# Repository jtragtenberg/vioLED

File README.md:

# vioLED
A guitar with LEDs on its frets

This instrument was developed by João Tragtenberg, Filipe Calegario from Batebit Artesania Digital (https://batebit.cc) in partnership with the string instruments luthier Rodrigo Veras (https://corpodusom.blogspot.com/) and the company Daccord Music Software (https://www.daccord.com.br/) as a first prototype for a acoustic guitar connected to a mobile app for educational purpuses.

Rodrigo his father and myself finishing the guitar

First time it lit

vioLED shining back to its maker Rodrigo Veras

Full lights in João's workshop

Example of chord progression mode

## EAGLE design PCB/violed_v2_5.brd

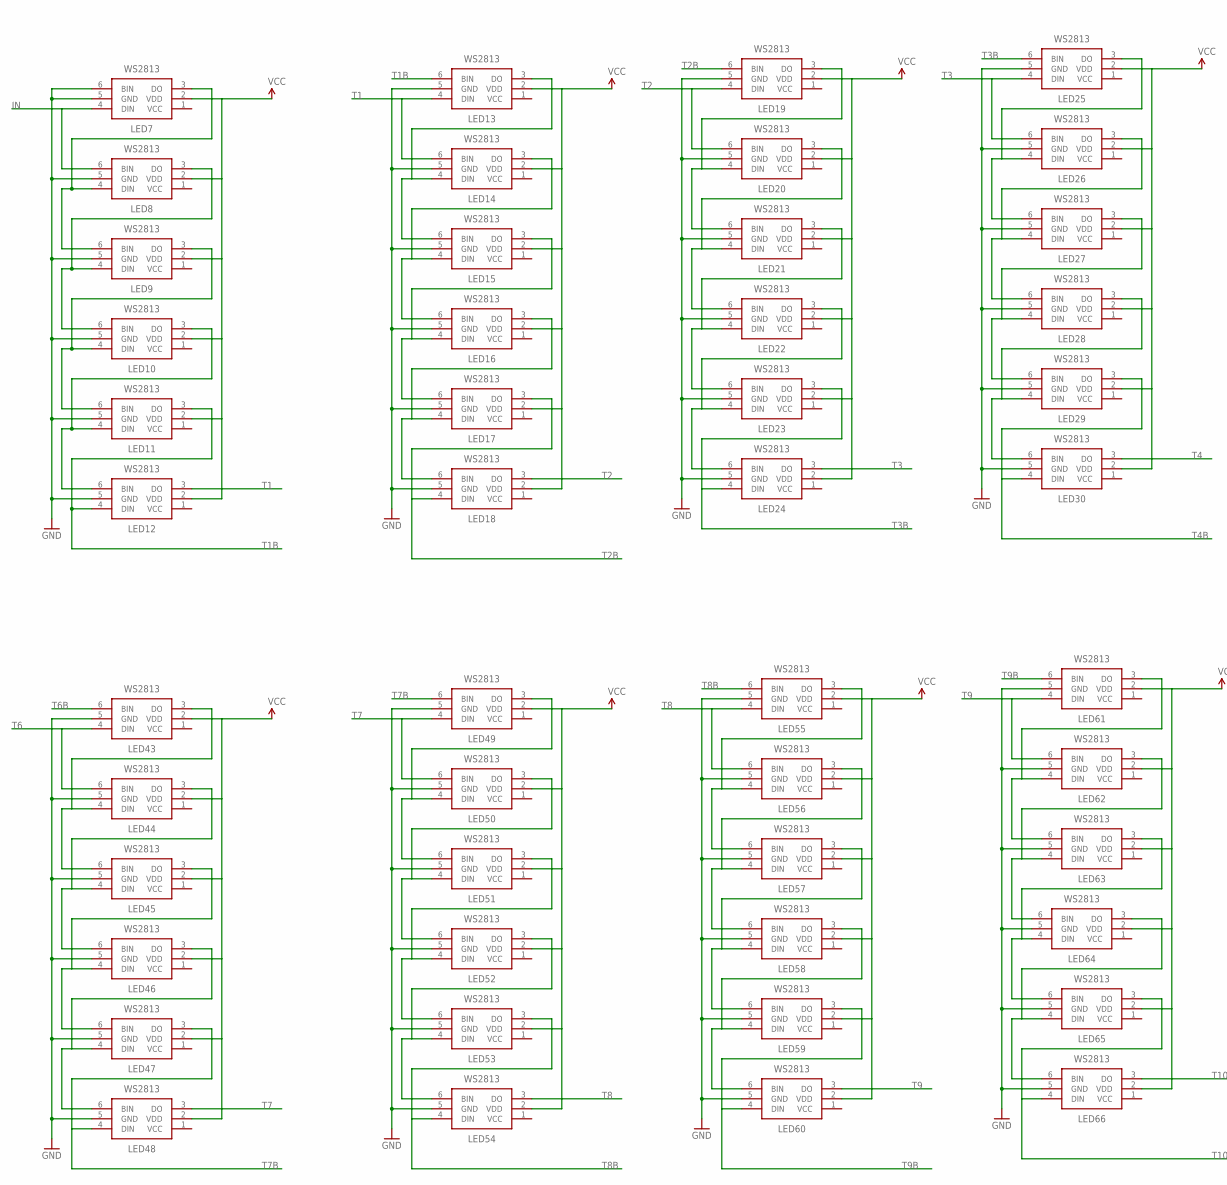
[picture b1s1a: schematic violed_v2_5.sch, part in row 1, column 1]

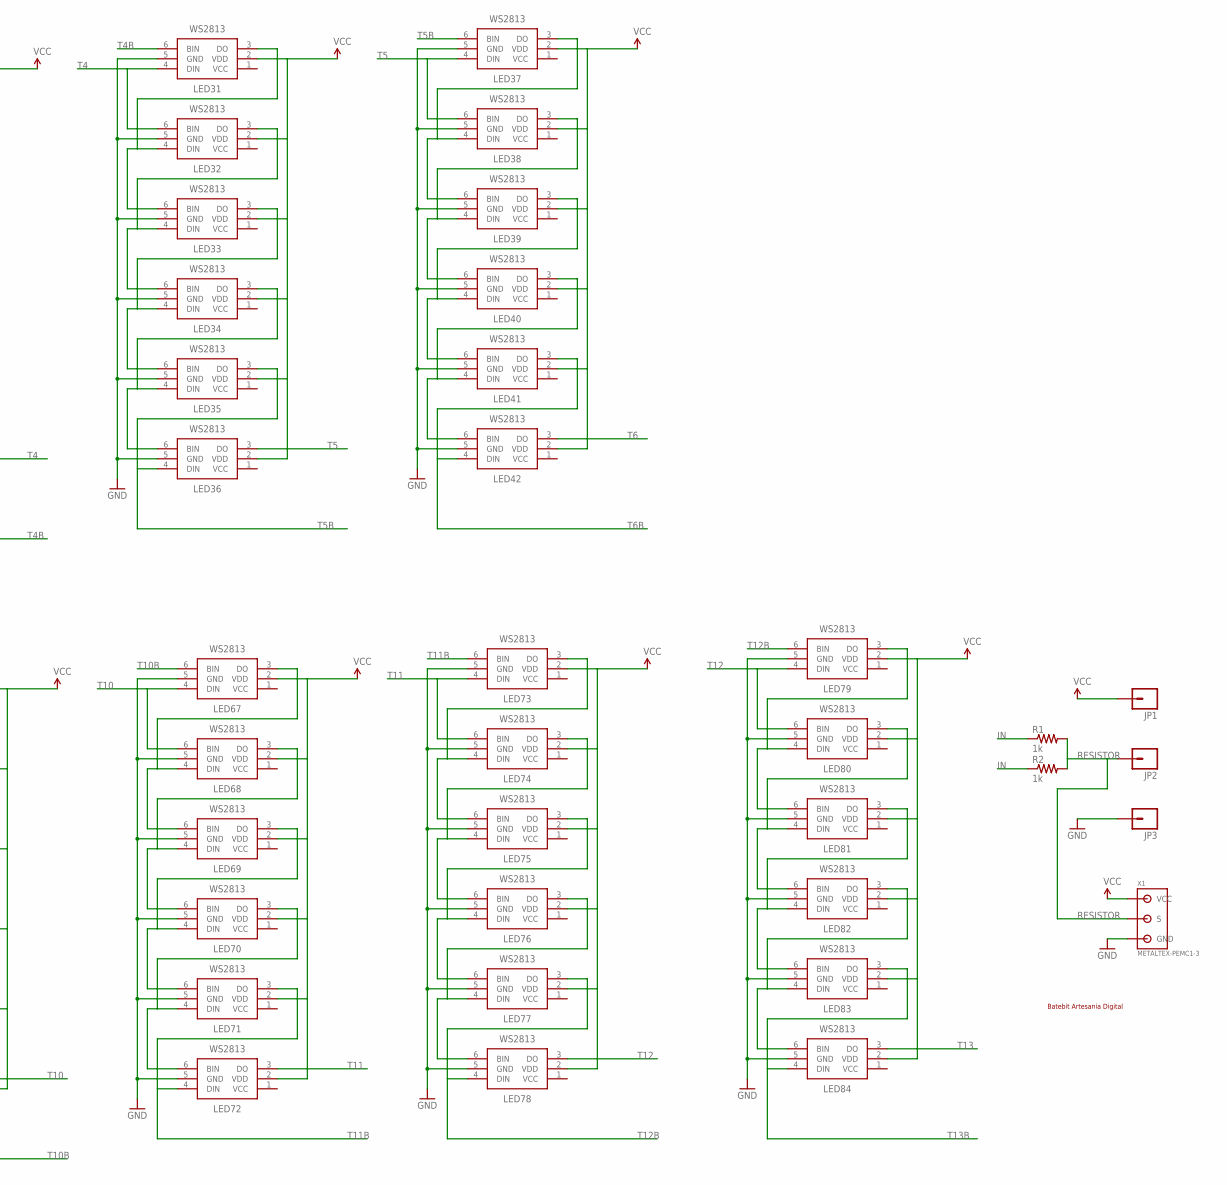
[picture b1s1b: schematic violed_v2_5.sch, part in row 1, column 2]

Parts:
JP1, JP2, JP3: M01PTH_LONGPAD; 1X01_LONGPAD
LED7, LED8, LED9, LED10, LED11, LED12, LED13, LED14, LED15, LED16, LED17, LED18, LED19, LED20, LED21, LED22, LED23, LED24, LED25, LED26, LED27, LED28, LED29, LED30, LED31, LED32, LED33, LED34, LED35, LED36, LED37, LED38, LED39, LED40, LED41, LED42, LED43, LED44, LED45, LED46, LED47, LED48, LED49, LED50, LED51, LED52, LED53, LED54, LED55, LED56, LED57, LED58, LED59, LED60, LED61, LED62, LED63, LED64, LED65, LED66, LED67, LED68, LED69, LED70, LED71, LED72, LED73, LED74, LED75, LED76, LED77, LED78, LED79, LED80, LED81, LED82, LED83, LED84: WS2813; WS2812
R1: 1k; 0805
R2: 1k; AXIAL-0.4
U$1: BATEBITTOP; BATEBIT_MED_TOP_LAYER
X1: METALTEX-PEMC1-3; METALTEX-PEMC1-3-PACKAGE-LONG-PAD

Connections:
GND: JP3.1, LED7.5 (GND), LED7.6 (BIN), LED8.5 (GND), LED9.5 (GND), LED10.5 (GND), LED11.5 (GND), LED12.5 (GND), LED13.5 (GND), LED14.5 (GND), LED15.5 (GND), LED16.5 (GND), LED17.5 (GND), LED18.5 (GND), LED19.5 (GND), LED20.5 (GND), LED21.5 (GND), LED22.5 (GND), LED23.5 (GND), LED24.5 (GND), LED25.5 (GND), LED26.5 (GND), LED27.5 (GND), LED28.5 (GND), LED29.5 (GND), LED30.5 (GND), LED31.5 (GND), LED32.5 (GND), LED33.5 (GND), LED34.5 (GND), LED35.5 (GND), LED36.5 (GND), LED37.5 (GND), LED38.5 (GND), LED39.5 (GND), LED40.5 (GND), LED41.5 (GND), LED42.5 (GND), LED43.5 (GND), LED44.5 (GND), LED45.5 (GND), LED46.5 (GND), LED47.5 (GND), LED48.5 (GND), LED49.5 (GND), LED50.5 (GND), LED51.5 (GND), LED52.5 (GND), LED53.5 (GND), LED54.5 (GND), LED55.5 (GND), LED56.5 (GND), LED57.5 (GND), LED58.5 (GND), LED59.5 (GND), LED60.5 (GND), LED61.5 (GND), LED62.5 (GND), LED63.5 (GND), LED64.5 (GND), LED65.5 (GND), LED66.5 (GND), LED67.5 (GND), LED68.5 (GND), LED69.5 (GND), LED70.5 (GND), LED71.5 (GND), LED72.5 (GND), LED73.5 (GND), LED74.5 (GND), LED75.5 (GND), LED76.5 (GND), LED77.5 (GND), LED78.5 (GND), LED79.5 (GND), LED80.5 (GND), LED81.5 (GND), LED82.5 (GND), LED83.5 (GND), LED84.5 (GND), X1.1 (GND)
IN: LED7.4 (DIN), LED8.6 (BIN), R1.1, R2.P$1 (1)
unnamed: LED7.3 (DO), LED8.4 (DIN), LED9.6 (BIN)
unnamed: LED8.3 (DO), LED9.4 (DIN), LED10.6 (BIN)
unnamed: LED9.3 (DO), LED10.4 (DIN), LED11.6 (BIN)
unnamed: LED10.3 (DO), LED11.4 (DIN), LED12.6 (BIN)
unnamed: LED13.3 (DO), LED14.4 (DIN), LED15.6 (BIN)
unnamed: LED14.3 (DO), LED15.4 (DIN), LED16.6 (BIN)
unnamed: LED15.3 (DO), LED16.4 (DIN), LED17.6 (BIN)
unnamed: LED16.3 (DO), LED17.4 (DIN), LED18.6 (BIN)
unnamed: LED19.3 (DO), LED20.4 (DIN), LED21.6 (BIN)
unnamed: LED20.3 (DO), LED21.4 (DIN), LED22.6 (BIN)
unnamed: LED21.3 (DO), LED22.4 (DIN), LED23.6 (BIN)
unnamed: LED22.3 (DO), LED23.4 (DIN), LED24.6 (BIN)
unnamed: LED25.3 (DO), LED26.4 (DIN), LED27.6 (BIN)
unnamed: LED26.3 (DO), LED27.4 (DIN), LED28.6 (BIN)
unnamed: LED27.3 (DO), LED28.4 (DIN), LED29.6 (BIN)
unnamed: LED28.3 (DO), LED29.4 (DIN), LED30.6 (BIN)
unnamed: LED31.3 (DO), LED32.4 (DIN), LED33.6 (BIN)
unnamed: LED32.3 (DO), LED33.4 (DIN), LED34.6 (BIN)
unnamed: LED33.3 (DO), LED34.4 (DIN), LED35.6 (BIN)
unnamed: LED34.3 (DO), LED35.4 (DIN), LED36.6 (BIN)
unnamed: LED37.3 (DO), LED38.4 (DIN), LED39.6 (BIN)
unnamed: LED38.3 (DO), LED39.4 (DIN), LED40.6 (BIN)
unnamed: LED39.3 (DO), LED40.4 (DIN), LED41.6 (BIN)
unnamed: LED40.3 (DO), LED41.4 (DIN), LED42.6 (BIN)
unnamed: LED43.3 (DO), LED44.4 (DIN), LED45.6 (BIN)
unnamed: LED44.3 (DO), LED45.4 (DIN), LED46.6 (BIN)
unnamed: LED45.3 (DO), LED46.4 (DIN), LED47.6 (BIN)
unnamed: LED46.3 (DO), LED47.4 (DIN), LED48.6 (BIN)
unnamed: LED49.3 (DO), LED50.4 (DIN), LED51.6 (BIN)
unnamed: LED50.3 (DO), LED51.4 (DIN), LED52.6 (BIN)
unnamed: LED51.3 (DO), LED52.4 (DIN), LED53.6 (BIN)
unnamed: LED52.3 (DO), LED53.4 (DIN), LED54.6 (BIN)
unnamed: LED55.3 (DO), LED56.4 (DIN), LED57.6 (BIN)
unnamed: LED56.3 (DO), LED57.4 (DIN), LED58.6 (BIN)
unnamed: LED57.3 (DO), LED58.4 (DIN), LED59.6 (BIN)
unnamed: LED58.3 (DO), LED59.4 (DIN), LED60.6 (BIN)
unnamed: LED61.3 (DO), LED62.4 (DIN), LED63.6 (BIN)
unnamed: LED62.3 (DO), LED63.4 (DIN), LED64.6 (BIN)
unnamed: LED63.3 (DO), LED64.4 (DIN), LED65.6 (BIN)
unnamed: LED64.3 (DO), LED65.4 (DIN), LED66.6 (BIN)
unnamed: LED67.3 (DO), LED68.4 (DIN), LED69.6 (BIN)
unnamed: LED68.3 (DO), LED69.4 (DIN), LED70.6 (BIN)
unnamed: LED69.3 (DO), LED70.4 (DIN), LED71.6 (BIN)
unnamed: LED70.3 (DO), LED71.4 (DIN), LED72.6 (BIN)
unnamed: LED73.3 (DO), LED74.4 (DIN), LED75.6 (BIN)
unnamed: LED74.3 (DO), LED75.4 (DIN), LED76.6 (BIN)
unnamed: LED75.3 (DO), LED76.4 (DIN), LED77.6 (BIN)
unnamed: LED76.3 (DO), LED77.4 (DIN), LED78.6 (BIN)
unnamed: LED79.3 (DO), LED80.4 (DIN), LED81.6 (BIN)
unnamed: LED80.3 (DO), LED81.4 (DIN), LED82.6 (BIN)
unnamed: LED81.3 (DO), LED82.4 (DIN), LED83.6 (BIN)
unnamed: LED82.3 (DO), LED83.4 (DIN), LED84.6 (BIN)
RESISTOR: JP2.1, R1.2, R2.P$2 (2), X1.2 (S)
T1: LED12.3 (DO), LED13.4 (DIN), LED14.6 (BIN)
T1B: LED11.3 (DO), LED12.4 (DIN), LED13.6 (BIN)
T2: LED18.3 (DO), LED19.4 (DIN), LED20.6 (BIN)
T2B: LED17.3 (DO), LED18.4 (DIN), LED19.6 (BIN)
T3: LED24.3 (DO), LED25.4 (DIN), LED26.6 (BIN)
T3B: LED23.3 (DO), LED24.4 (DIN), LED25.6 (BIN)
T4: LED30.3 (DO), LED31.4 (DIN), LED32.6 (BIN)
T4B: LED29.3 (DO), LED30.4 (DIN), LED31.6 (BIN)
T5: LED36.3 (DO), LED37.4 (DIN), LED38.6 (BIN)
T5B: LED35.3 (DO), LED36.4 (DIN), LED37.6 (BIN)
T6: LED42.3 (DO), LED43.4 (DIN), LED44.6 (BIN)
T6B: LED41.3 (DO), LED42.4 (DIN), LED43.6 (BIN)
T7: LED48.3 (DO), LED49.4 (DIN), LED50.6 (BIN)
T7B: LED47.3 (DO), LED48.4 (DIN), LED49.6 (BIN)
T8: LED54.3 (DO), LED55.4 (DIN), LED56.6 (BIN)
T8B: LED53.3 (DO), LED54.4 (DIN), LED55.6 (BIN)
T9: LED60.3 (DO), LED61.4 (DIN), LED62.6 (BIN)
T9B: LED59.3 (DO), LED60.4 (DIN), LED61.6 (BIN)
T10: LED66.3 (DO), LED67.4 (DIN), LED68.6 (BIN)
T10B: LED65.3 (DO), LED66.4 (DIN), LED67.6 (BIN)
T11: LED72.3 (DO), LED73.4 (DIN), LED74.6 (BIN)
T11B: LED71.3 (DO), LED72.4 (DIN), LED73.6 (BIN)
T12: LED78.3 (DO), LED79.4 (DIN), LED80.6 (BIN)
T12B: LED77.3 (DO), LED78.4 (DIN), LED79.6 (BIN)
T13: LED84.3 (DO)
T13B: LED83.3 (DO), LED84.4 (DIN)
VCC: JP1.1, LED7.2 (VDD), LED8.2 (VDD), LED9.2 (VDD), LED10.2 (VDD), LED11.2 (VDD), LED12.2 (VDD), LED13.2 (VDD), LED14.2 (VDD), LED15.2 (VDD), LED16.2 (VDD), LED17.2 (VDD), LED18.2 (VDD), LED19.2 (VDD), LED20.2 (VDD), LED21.2 (VDD), LED22.2 (VDD), LED23.2 (VDD), LED24.2 (VDD), LED25.2 (VDD), LED26.2 (VDD), LED27.2 (VDD), LED28.2 (VDD), LED29.2 (VDD), LED30.2 (VDD), LED31.2 (VDD), LED32.2 (VDD), LED33.2 (VDD), LED34.2 (VDD), LED35.2 (VDD), LED36.2 (VDD), LED37.2 (VDD), LED38.2 (VDD), LED39.2 (VDD), LED40.2 (VDD), LED41.2 (VDD), LED42.2 (VDD), LED43.2 (VDD), LED44.2 (VDD), LED45.2 (VDD), LED46.2 (VDD), LED47.2 (VDD), LED48.2 (VDD), LED49.2 (VDD), LED50.2 (VDD), LED51.2 (VDD), LED52.2 (VDD), LED53.2 (VDD), LED54.2 (VDD), LED55.2 (VDD), LED56.2 (VDD), LED57.2 (VDD), LED58.2 (VDD), LED59.2 (VDD), LED60.2 (VDD), LED61.2 (VDD), LED62.2 (VDD), LED63.2 (VDD), LED64.2 (VDD), LED65.2 (VDD), LED66.2 (VDD), LED67.2 (VDD), LED68.2 (VDD), LED69.2 (VDD), LED70.2 (VDD), LED71.2 (VDD), LED72.2 (VDD), LED73.2 (VDD), LED74.2 (VDD), LED75.2 (VDD), LED76.2 (VDD), LED77.2 (VDD), LED78.2 (VDD), LED79.2 (VDD), LED80.2 (VDD), LED81.2 (VDD), LED82.2 (VDD), LED83.2 (VDD), LED84.2 (VDD), X1.3 (VCC)

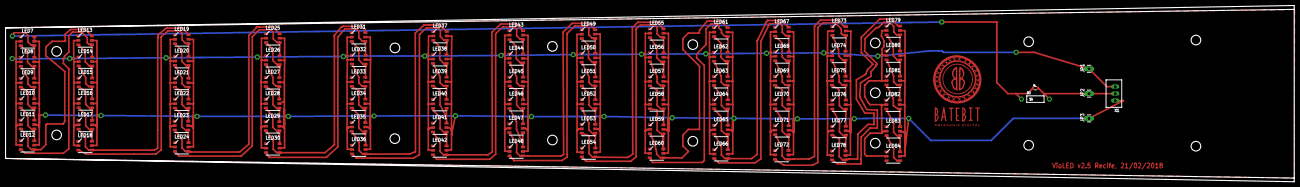
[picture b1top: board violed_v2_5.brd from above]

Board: 2 copper layers, 468.0 x 64.0 mm, 85 parts (0 on the bottom side), 81 nets.

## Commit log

2021-05-18 upload files
